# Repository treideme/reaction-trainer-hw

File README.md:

# Next-Generation Reaction Trainer

This repository contains the hardware design, such as PCB files and
mechanical CAD files for the IoT contest. 

Please see my [blog post](https://reidemeister.com/blog/2023.06.06)
for a detailed run-down of the design.

## Requirements 
 * Kicad 6+
 * my fork of [WCH Kicad LBR](https://github.com/treideme/wch-kicad-lbr) to get CH32V208W library parts
   * Big shout out to [sad-electronics](https://github.com/sad-electronics) for laying the ground work

See [my blog post](https://www.reidemeister.com/?p=624) for more information and build updates.

 * [Firmware Sources and Overview](https://github.com/treideme/reaction-trainer)
 * [Android Application Sources](https://github.com/treideme/reaction-trainer-app)

## [Bringup](BRINGUP.md)

----
(C) 2023 Thomas Reidemeister, released under [CERN-OHL-P](LICENSE).

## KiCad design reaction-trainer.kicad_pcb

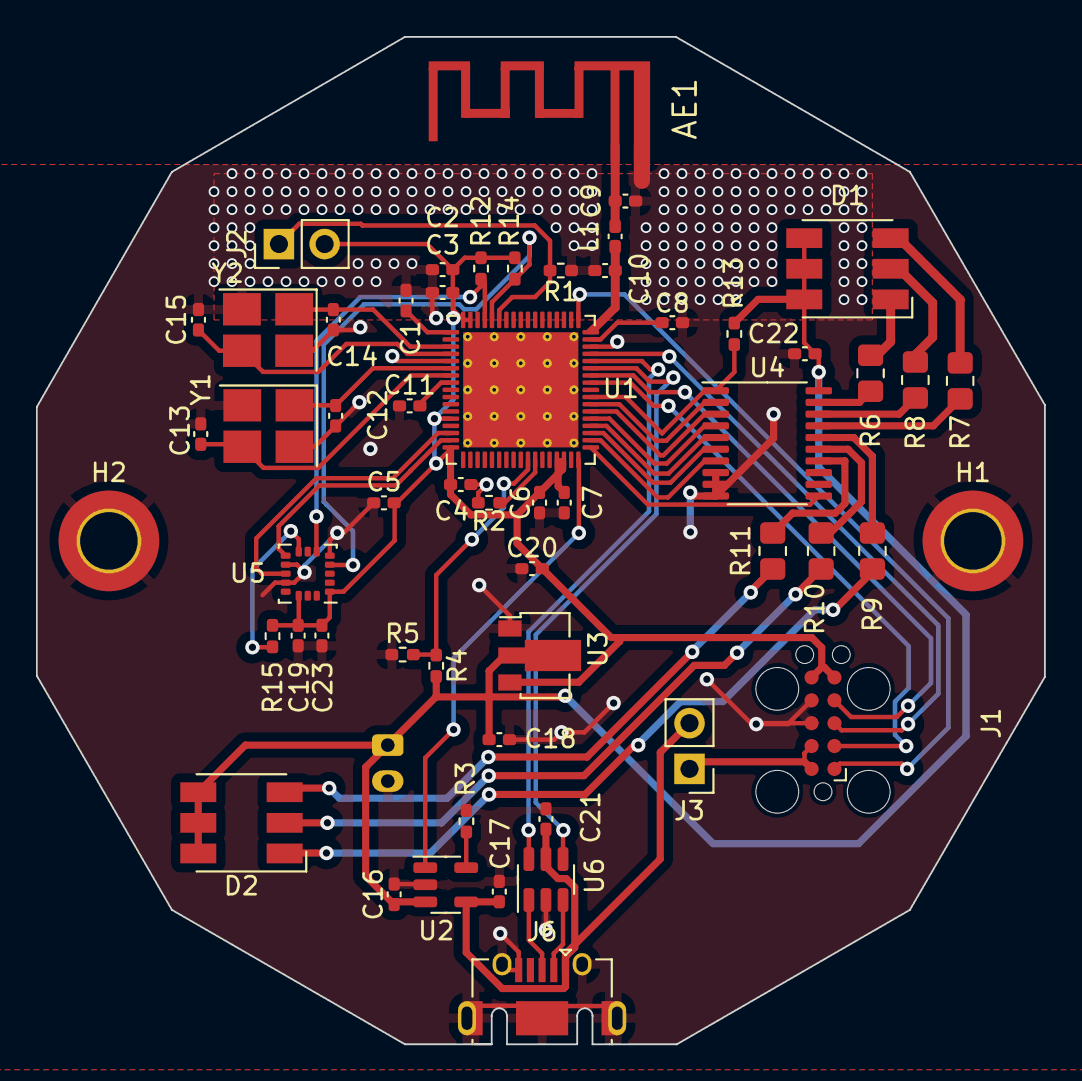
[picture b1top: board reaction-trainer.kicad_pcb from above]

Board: 2 copper layers, 56.0 x 56.0 mm, 57 parts (1 on the bottom side), 52 nets.

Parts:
AE1: Antenna_Shield; ANT-F-1-2.4G-1.6MM-FR4-WCH
C1, C2, C3, C4, C5, C6, C7, C11, C21, C22, C23: 0.1uF 20%; C_0402_1005Metric_Pad0.74x0.62mm_HandSolder
C8, C16, C17, C18, C19, C20: 10uF 20%; C_0402_1005Metric_Pad0.74x0.62mm_HandSolder
C9: 1.5pF 5%; C_0402_1005Metric_Pad0.74x0.62mm_HandSolder
C10: 1pF 5%; C_0402_1005Metric_Pad0.74x0.62mm_HandSolder
C12, C13: 12pF 5%; C_0402_1005Metric_Pad0.74x0.62mm_HandSolder
C14, C15: 15pF 5%; C_0402_1005Metric_Pad0.74x0.62mm_HandSolder
D1, D2: C784541; LED_RGB_5050-6
H1, H2: MountingHole_Pad; MountingHole_3.2mm_M3_DIN965_Pad_TopBottom
J1: TC2050; Tag-Connect_TC2050-IDC-FP_2x05_P1.27mm_Vertical
J2, J3: DNP; PinHeader_1x02_P2.54mm_Vertical
J5: JST_PH_B2B; JST_PH_B2B-PH-K_1x02_P2.00mm_Vertical
J6: 47590-0001; USB_Micro-AB_Molex_47590-0001
L1: 1.8nH; L_0402_1005Metric_Pad0.77x0.64mm_HandSolder
R1, R2, R3, R12, R13, R14, R15: 10K 5%; R_0402_1005Metric_Pad0.72x0.64mm_HandSolder
R4: 510K 1%; R_0402_1005Metric_Pad0.72x0.64mm_HandSolder
R5: 1M 1%; R_0402_1005Metric_Pad0.72x0.64mm_HandSolder
R6, R7, R9, R11: 15 5% 125mW; R_0805_2012Metric_Pad1.20x1.40mm_HandSolder
R8, R10: 30 5% 125mW; R_0805_2012Metric_Pad1.20x1.40mm_HandSolder
U1: CH32V208WBU6; QFN-68-1EP_8x8mm_P0.4mm_EP6.4x6.4mm_ThermalVias
U2: MCP73831-2-OT; SOT-23-5
U3: HT7533-1; SOT-89-3
U4: 74HC573PW,118; TSSOP-20_4.4x6.5mm_P0.65mm
U5: LIS3DHTR; LGA-16_3x3mm_P0.5mm_LayoutBorder3x5y
U6: USBLC6-2SC6; SOT-23-6
Y1: 32MHz; Crystal_SMD_3225-4Pin_3.2x2.5mm_HandSoldering
Y2: 32768Hz; Crystal_SMD_3225-4Pin_3.2x2.5mm_HandSoldering

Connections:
+3V3: C2.1, C3.1, C4.1, C5.2, C6.1, C7.1, C19.2, C20.2, C23.2, J1.5, J1.6, J2.2, R12.1, R14.2, R15.2, U1.13 (VDDA), U1.17 (VIO_4), U1.31 (VIO_1), U1.32 (VDD_1), U1.67 (VIO_3), U1.68 (VDD_3), U3.3 (VOUT), U5.1 (VDD_IO), U5.14 (VDD)
+5V: C17.1, C21.2, J3.2, J6.1 (VBUS), U2.4 (VDD), U6.5 (VBUS)
+BATT: C16.1, C18.2, C22.2, D1.4 (BA), D1.5 (GA), D1.6 (RA), D2.4 (BA), D2.5 (GA), D2.6 (RA), J5.1, R4.2, R13.1, U2.3 (VBAT), U3.2 (VIN), U4.20 (VCC)
/CH32V208W/ANT: AE1.1 (A), C9.1, L1.1
/CH32V208W/ANT1: C10.1, L1.2, U1.51 (ANT)
/CH32V208W/BOOT0: J2.1, R1.2, U1.63 (BOOT0)
/CH32V208W/LED_0: U1.41 (PC8/TXP), U4.2 (D0)
/CH32V208W/LED_1: U1.40 (PC7/RXN), U4.3 (D1)
/CH32V208W/LED_2: U1.39 (PC6/RXP), U4.4 (D2)
/CH32V208W/LED_3: U1.38 (PB15), U4.5 (D3)
/CH32V208W/LED_4: U1.37 (PB14), U4.6 (D4)
/CH32V208W/LED_5: U1.36 (PB13), U4.7 (D5)
/CH32V208W/LED_EN: R13.2, U1.42 (PC9/TXN), U4.1 (OE)
/CH32V208W/LED_LATCH: U1.35 (PB12), U4.11 (Load)
/CH32V208W/MOTION_INT1: U1.15 (PA1/ADC1), U5.11 (INT1)
/CH32V208W/MOTION_INT2: U1.16 (PA2/ADC2), U5.9 (INT2)
/CH32V208W/NRST: C11.2, U1.8 (NRST)
/CH32V208W/OSC32_IN: C14.2, U1.3 (PC14/OSC32IN), Y2.1
/CH32V208W/OSC32_OUT: C15.2, U1.4 (PC15/PSC32OUT), Y2.3
/CH32V208W/OSC_IN: C12.2, U1.6 (OSC_IN), Y1.1
/CH32V208W/OSC_OUT: C13.2, U1.7 (OSC_OUT), Y1.3
/CH32V208W/RXD: J1.4, U1.45 (PA10)
/CH32V208W/SCL: R14.1, U1.64 (PB8), U5.4 (SCL/SPC)
/CH32V208W/SDA: R12.2, U1.65 (PB9), U5.6 (SDA/SDI/SDO)
/CH32V208W/STAT: U1.34 (PD6), U2.1 (STAT)
/CH32V208W/SWCK: J1.1, U1.52 (PA14/SWCLK)
/CH32V208W/SWIO: J1.3, U1.48 (PA13/SWDIO)
/CH32V208W/TXD: J1.2, U1.44 (PA9)
/CH32V208W/USBDM: U1.46 (PA11/USB1DM), U6.4 (I/O2)
/CH32V208W/USBDP: U1.47 (PA12/USB1DP), U6.6 (I/O1)
/CH32V208W/VSENSE: R4.1, R5.2, U1.27 (PB1/ADC9)
/USB/DN_IN: J6.2 (D-), U6.3 (I/O2)
/USB/DP_IN: J6.3 (D+), U6.1 (I/O1)
GND: AE1.2 (Shield), C1.1, C2.2, C3.2, C4.2, C5.1, C6.2, C7.2, C8.1, C9.2, C10.2, C11.1, C12.1, C13.1, C14.1, C15.1, C16.2, C17.2, C18.1, C19.1, C20.1, C21.1, C22.1, C23.1, H1.1, H2.1, J1.7, J1.8, J5.2, J6.5 (GND), J6.6 (Shield), R1.1, R2.2, R3.1, R5.1, U1.5 (VSSA), U1.49 (VSS_2), U1.69 (GND), U2.2 (VSS), U3.1 (GND), U4.8 (D6), U4.9 (D7), U4.10 (GND), U5.5 (GND), U5.10 (GND), U5.12 (GND), U6.2 (GND), Y1.2, Y1.4, Y2.2, Y2.4
unnamed: D1.3 (BK), R7.2
unnamed: D1.2 (GK), R8.2
unnamed: D1.1 (RK), R6.2
unnamed: D2.3 (BK), R11.2
unnamed: D2.2 (GK), R10.2
unnamed: D2.1 (RK), R9.2
unnamed: J1.9, J1.10, J3.1
unnamed: R2.1, U1.28 (PB2/BOOT1)
unnamed: C1.2, U1.1 (VBAT)
unnamed: C8.2, U1.50 (VINTA)
unnamed: R3.2, U2.5 (PROG)
unnamed: R6.1, U4.19 (Q0)
unnamed: R8.1, U4.18 (Q1)
unnamed: R7.1, U4.17 (Q2)
unnamed: R9.1, U4.16 (Q3)
unnamed: R10.1, U4.15 (Q4)
unnamed: R11.1, U4.14 (Q5)
unnamed: R15.1, U5.8 (CS)

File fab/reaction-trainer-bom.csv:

"Reference","Value","Footprint","Datasheet","JLCPCB Part #","Qty"
"AE1","Antenna_Shield","wch-antenna-pretty:ANT-F-1-2.4G-1.6MM-FR4-WCH","~","","1"
"C1-C7, C11, C21-C23","0.1uF 20%","Capacitor_SMD:C_0402_1005Metric_Pad0.74x0.62mm_HandSolder","https://www.lcsc.com/product-detail/Multilayer-Ceramic-Capac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","C359190","11"
"C8, C16-C20","10uF 20%","Capacitor_SMD:C_0402_1005Metric_Pad0.74x0.62mm_HandSolder","https://www.lcsc.com/product-detail/Multilayer-Ceramic-Capac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","C315248","6"
"C9","1.5pF 5%","Capacitor_SMD:C_0402_1005Metric_Pad0.74x0.62mm_HandSolder","https://www.lcsc.com/product-detail/Multilayer-Ceramic-Capac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","C170150","1"
"C10","1pF 5%","Capacitor_SMD:C_0402_1005Metric_Pad0.74x0.62mm_HandSolder","https://www.lcsc.com/product-detail/Multilayer-Ceramic-Capac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","C307340","1"
"C12, C13","12pF 5%","Capacitor_SMD:C_0402_1005Metric_Pad0.74x0.62mm_HandSolder","https://www.lcsc.com/product-detail/Multilayer-Ceramic-Capac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","C472446","2"
"C14, C15","15pF 5%","Capacitor_SMD:C_0402_1005Metric_Pad0.74x0.62mm_HandSolder","https://www.lcsc.com/product-detail/Multilayer-Ceramic-Capac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","C86285","2"
"D1, D2","C784541","LED_SMD:LED_RGB_5050-6","https://www.lcsc.com/product-detail/Light-Emitting-Diodes-LE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","C784541","2"
"H1, H2","MountingHole_Pad","MountingHole:MountingHole_3.2mm_M3_DIN965_Pad_TopBottom","~","","2"
"J1","TC2050","Connector:Tag-Connect_TC2050-IDC-FP_2x05_P1.27mm_Vertical","https://www.tag-connect.com/wp-content/uploads/bsk-pdf-manag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","","1"
"J2, J3","DNP","Connector_PinHeader_2.54mm:PinHeader_1x02_P2.54mm_Vertical","~","","2"
"J5","JST_PH_B2B","Connector_JST:JST_PH_B2B-PH-K_1x02_P2.00mm_Vertical","https://www.lcsc.com/product-detail/Wire-To-Board-Wire-To-Wi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","C131337","1"
"J6","47590-0001","Connector_USB:USB_Micro-AB_Molex_47590-0001","https://www.lcsc.com/product-detail/USB-Connectors_MOLEX-475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","C136001","1"
"L1","1.8nH","Inductor_SMD:L_0402_1005Metric_Pad0.77x0.64mm_HandSolder","https://www.lcsc.com/product-detail/Inductors-SMD_TDK-MLG100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","C87530","1"
"R1-R3, R12-R15","10K 5%","Resistor_SMD:R_0402_1005Metric_Pad0.72x0.64mm_HandSolder","https://www.lcsc.com/product-detail/Chip-Resistor-Surface-Mo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","C2906885","7"
"R4","510K 1%","Resistor_SMD:R_0402_1005Metric_Pad0.72x0.64mm_HandSolder","https://www.lcsc.com/product-detail/Chip-Resistor-Surface-Mo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","C2909365","1"
"R5","1M 1%","Resistor_SMD:R_0402_1005Metric_Pad0.72x0.64mm_HandSolder","https://www.lcsc.com/product-detail/Chip-Resistor-Surface-Mo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","C2906900","1"
"R6, R7, R9, R11","15 5% 125mW","Resistor_SMD:R_0805_2012Metric_Pad1.20x1.40mm_HandSolder","https://www.lcsc.com/product-detail/Chip-Resistor-Surface-Mo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","C2930246","4"
"R8, R10","30 5% 125mW","Resistor_SMD:R_0805_2012Metric_Pad1.20x1.40mm_HandSolder","https://www.lcsc.com/product-detail/Chip-Resistor-Surface-Mo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","C2930273","2"
"U1","CH32V208WBU6","Package_DFN_QFN:QFN-68-1EP_8x8mm_P0.4mm_EP6.4x6.4mm_ThermalVias","http://www.wch-ic.com/downloads/CH32V208DS0_PDF.html","C5187528","1"
"U2","MCP73831-2-OT","Package_TO_SOT_SMD:SOT-23-5","http://ww1.microchip.com/downloads/en/DeviceDoc/20001984g.pdf","C424093","1"
"U3","HT7533-1","Package_TO_SOT_SMD:SOT-89-3","https://www.holtek.com/documents/10179/116711/HT75xx-1v250.pdf","C14289","1"
"U4","74HC573PW,118","Package_SO:TSSOP-20_4.4x6.5mm_P0.65mm","74xx/74hc573.pdf","C5944","1"
"U5","LIS3DHTR","Package_LGA:LGA-16_3x3mm_P0.5mm_LayoutBorder3x5y","https://www.st.com/resource/en/datasheet/cd00274221.pdf","C15134","1"
"U6","USBLC6-2SC6","Package_TO_SOT_SMD:SOT-23-6","https://www.st.com/resource/en/datasheet/usblc6-2.pdf","C5250994","1"
"Y1","32MHz","Crystal:Crystal_SMD_3225-4Pin_3.2x2.5mm_HandSoldering","https://www.lcsc.com/product-detail/Crystals_Yangxing-Tech-X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","C9009","1"
"Y2","32768Hz","Crystal:Crystal_SMD_3225-4Pin_3.2x2.5mm_HandSoldering","https://www.lcsc.com/product-detail/Oscillators_Yangxing-Tec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","C725996","1"

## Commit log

2022-07-17 Delta for future Debugger interfaces
2023-05-30 Preliminary framing and library parts
2023-05-31 Preliminary schematic modules
2023-05-31 Footprint fix, preliminary pcb
2023-06-01 Added PWM audio out
2023-06-01 Added Antenna design
2023-06-02 Removed audio, more routing
2023-06-03 Added JLPCB DRCs, antenna hatching
2023-06-05 Field updates, generating fab files
2023-06-05 Changed outline for DFM
2023-06-05 Added Manufacturing Files
2023-06-12 Added assembled PCB
2023-06-13 Bringup documentation added
2025-10-19 Updated for blog migration

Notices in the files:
reaction-trainer.kicad_pcb:
Released under CERN-OHL-P (see LICENSE)
